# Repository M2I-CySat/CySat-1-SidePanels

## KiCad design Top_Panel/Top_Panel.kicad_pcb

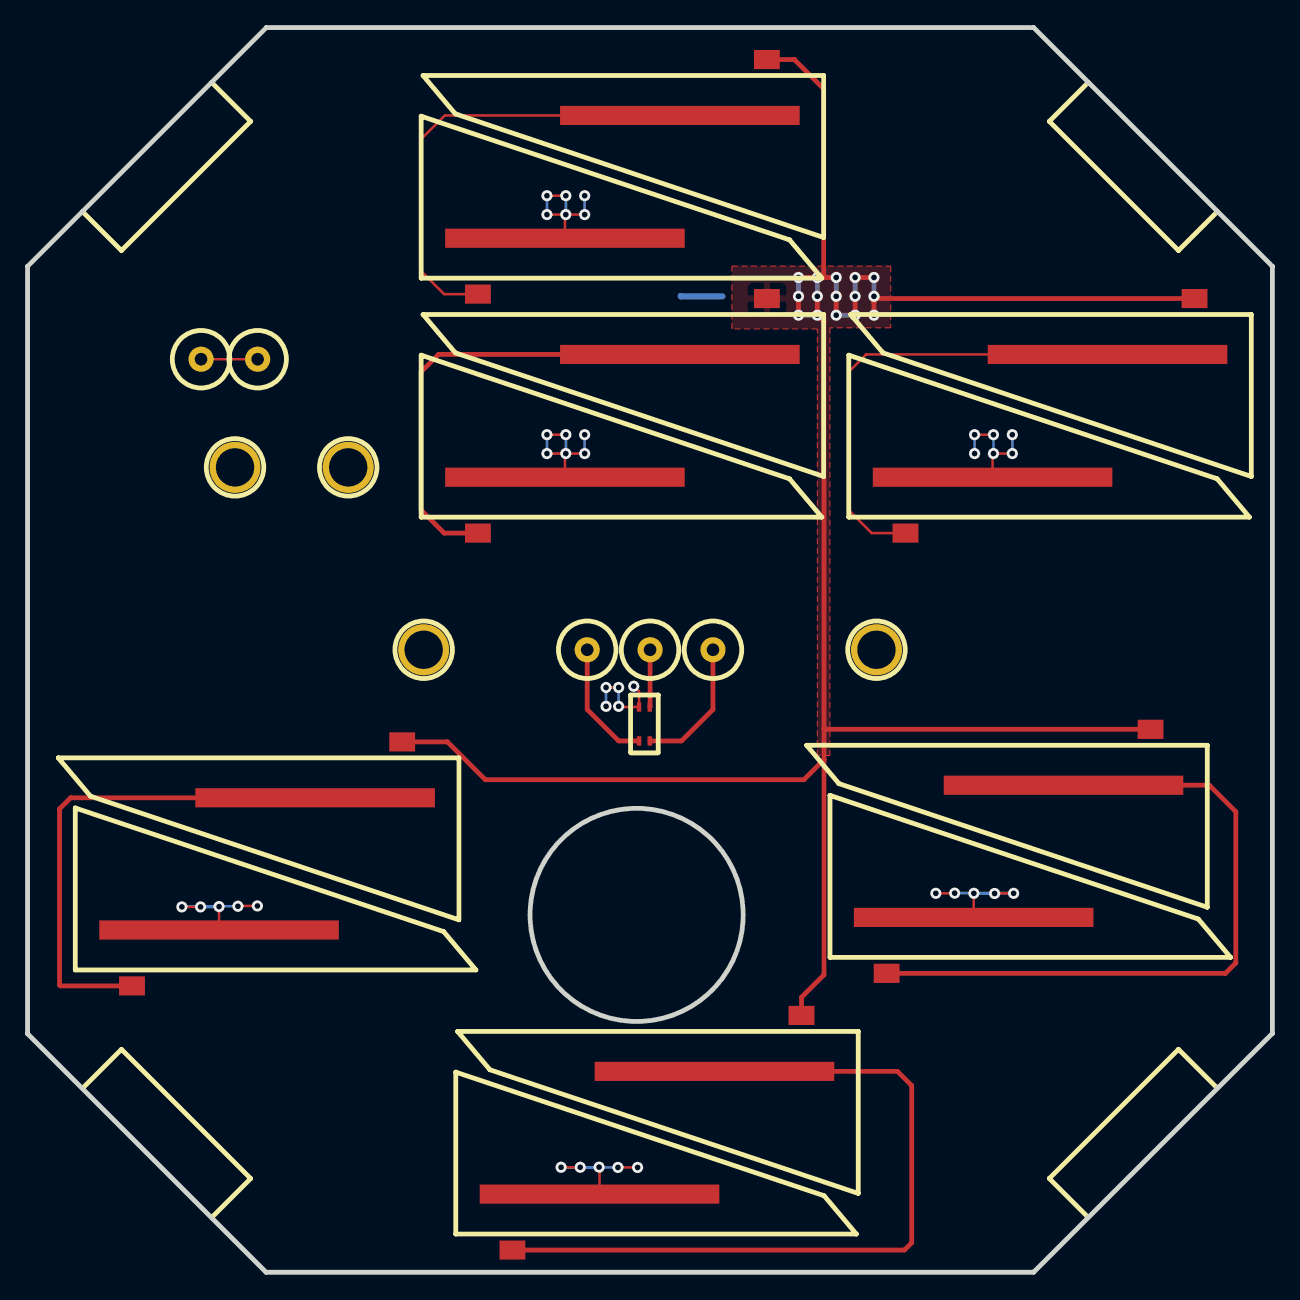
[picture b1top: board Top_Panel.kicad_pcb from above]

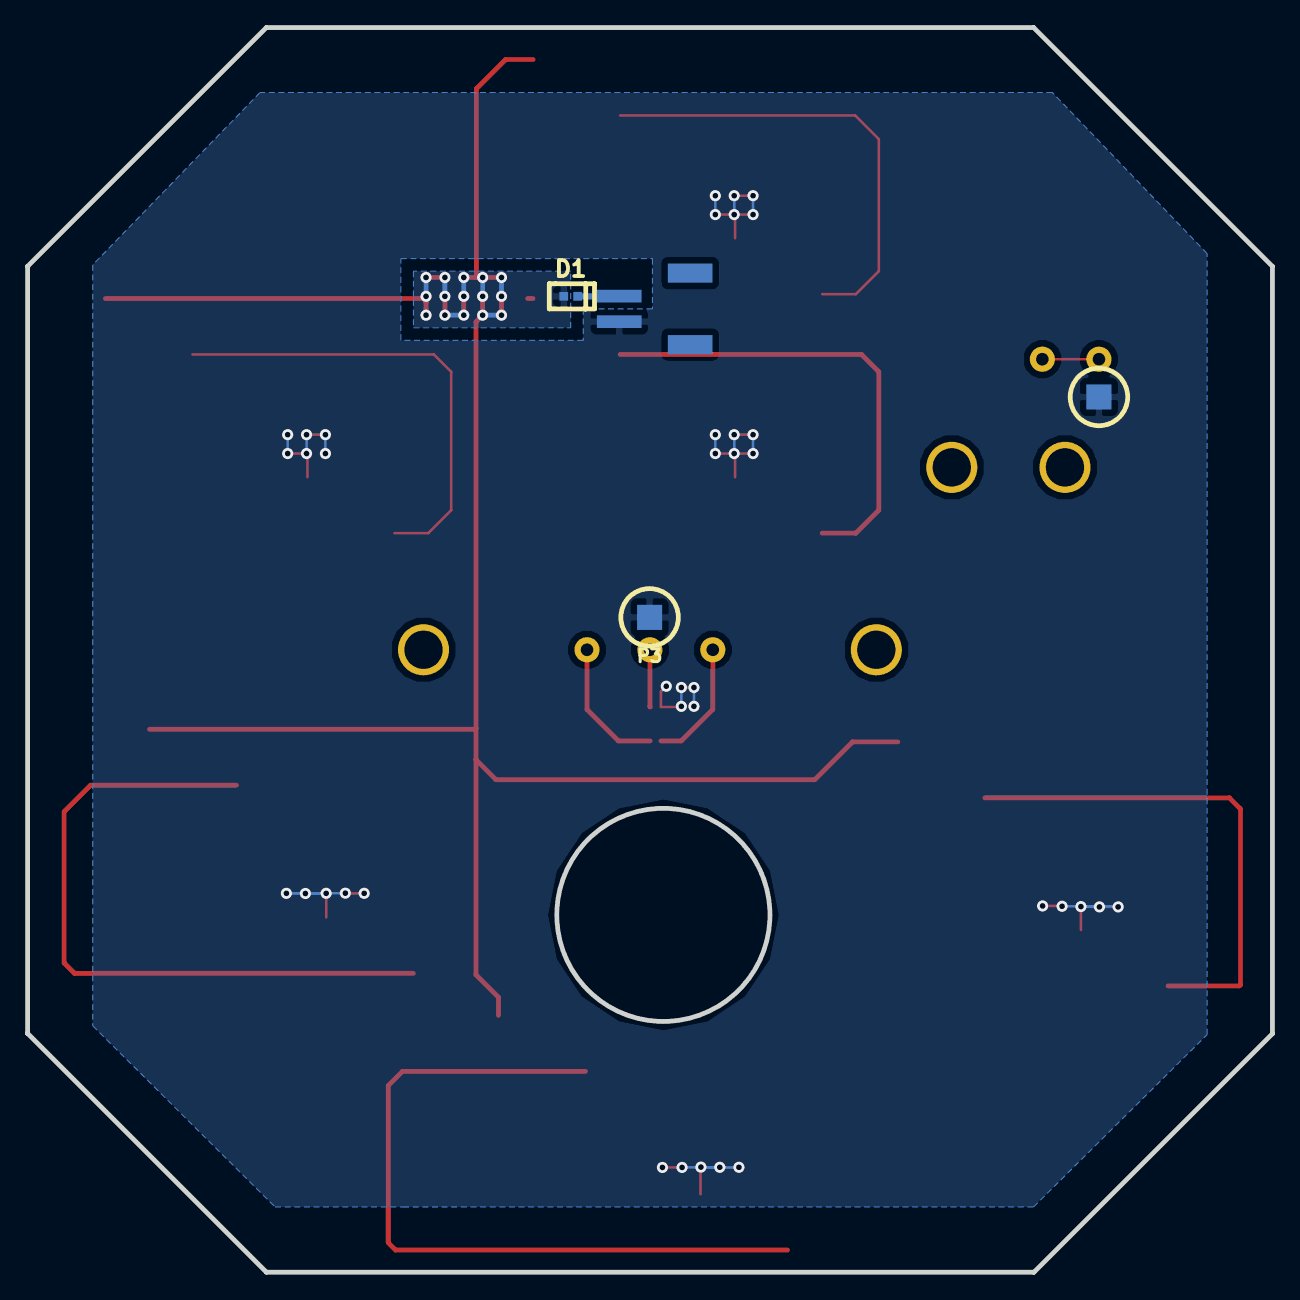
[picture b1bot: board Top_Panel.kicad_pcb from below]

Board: 2 copper layers, 99.0 x 99.0 mm, 26 parts (4 on the bottom side), 13 nets.

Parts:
1PIN, 1PIN#2, 1PIN#3, 1PIN#4: P***; 1pin
BAL1: ATB2012
D1: DIODE; DFN1006
P1: CONN_2; CONN_JST_2_SMD
P2, P3, P4, P5, P6, P7, P8: CONN_1; 1pin
S1, S2, S3, S4, S5, S6, S7, S8, S9, S10, S11, S12: SOLARCELL; SPECTROLAB_TASC2

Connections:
/Plus: D1.1, S2.1, S4.1, S6.1, S8.1, S10.1, S12.1
GND: BAL1.2, P1.1, P3.1, P8.1, S1.2, S3.2, S5.2, S7.2, S9.2, S11.2
unnamed: S1.1, S2.2
unnamed: S11.1, S12.2
unnamed: BAL1.4, P4.1
unnamed: BAL1.3, P5.1
unnamed: BAL1.1, P2.1
unnamed: D1.2, P1.2
unnamed: S9.1, S10.2
unnamed: S7.1, S8.2
unnamed: S5.1, S6.2
unnamed: S3.1, S4.2
unnamed: P6.1, P7.1

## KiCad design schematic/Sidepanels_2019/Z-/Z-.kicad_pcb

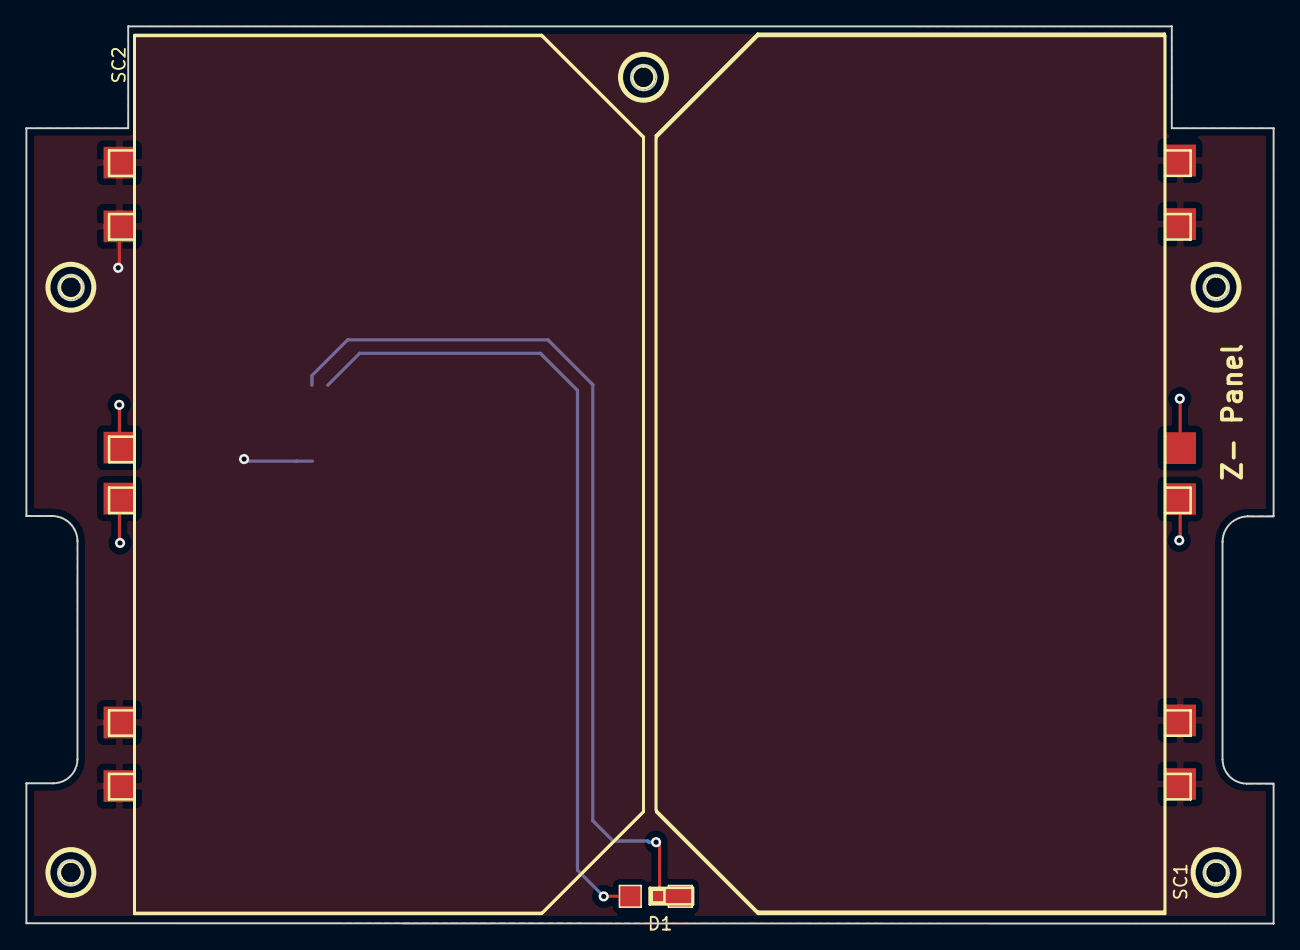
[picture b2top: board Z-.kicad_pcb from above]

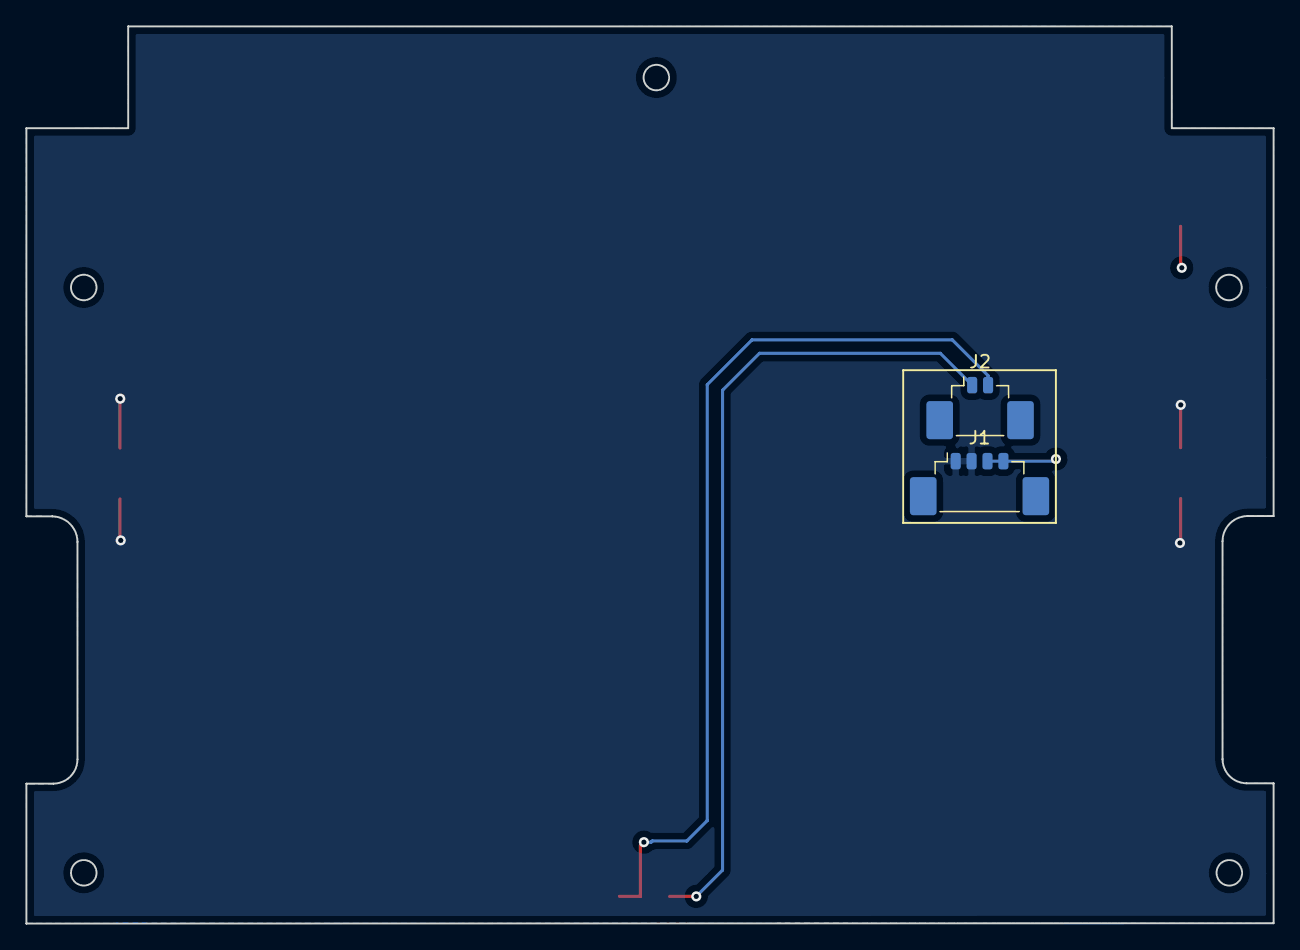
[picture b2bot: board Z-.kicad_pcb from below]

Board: 2 copper layers, 98.0 x 70.5 mm, 5 parts (2 on the bottom side), 4 nets.

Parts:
D1: D_Photo; Sun_Sensor
J1: Conn_01x04; Molex_PicoBlade_53398-0471_1x04-1MP_P1.25mm_Vertical
J2: Conn_01x02; Molex_PicoBlade_53398-0271_1x02-1MP_P1.25mm_Vertical
SC1, SC2: Solar_Cell; Spectrolab

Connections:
unnamed: D1.1, J2.2
unnamed: D1.2, J2.1
VCC: J1.3, J1.4, SC1.1, SC2.1
VSS: J1.1, J1.2, SC1.2, SC2.2
